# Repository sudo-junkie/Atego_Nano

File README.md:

# Atego Nano

KiCad 7 design files (schematic, PCB, gerber, BOM) for an Arduino Nano clone, with the following additional features:
-	Single cell lithium battery charger
-	VIN upto 15V
-	USB C
-	RGB LEDs

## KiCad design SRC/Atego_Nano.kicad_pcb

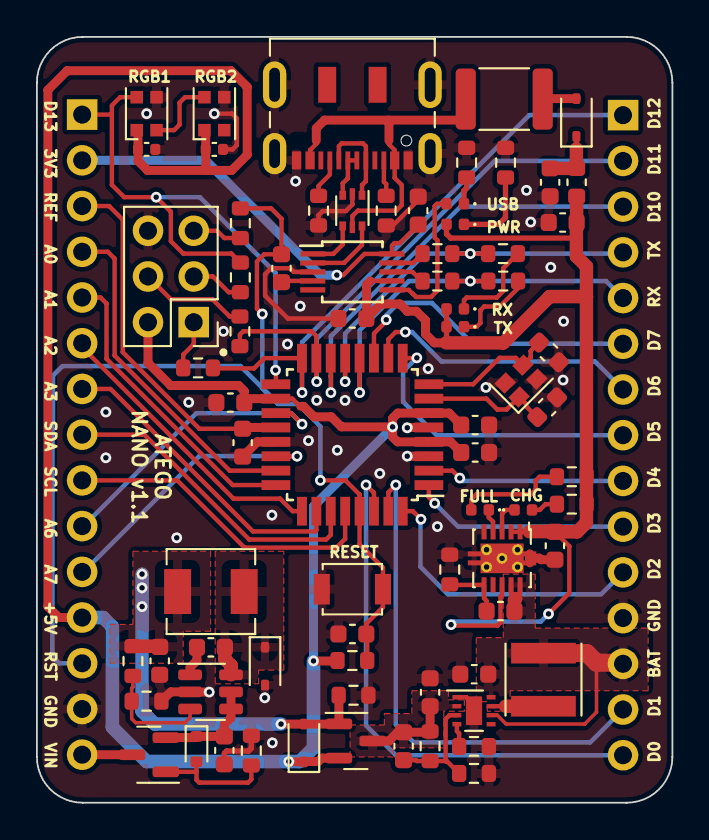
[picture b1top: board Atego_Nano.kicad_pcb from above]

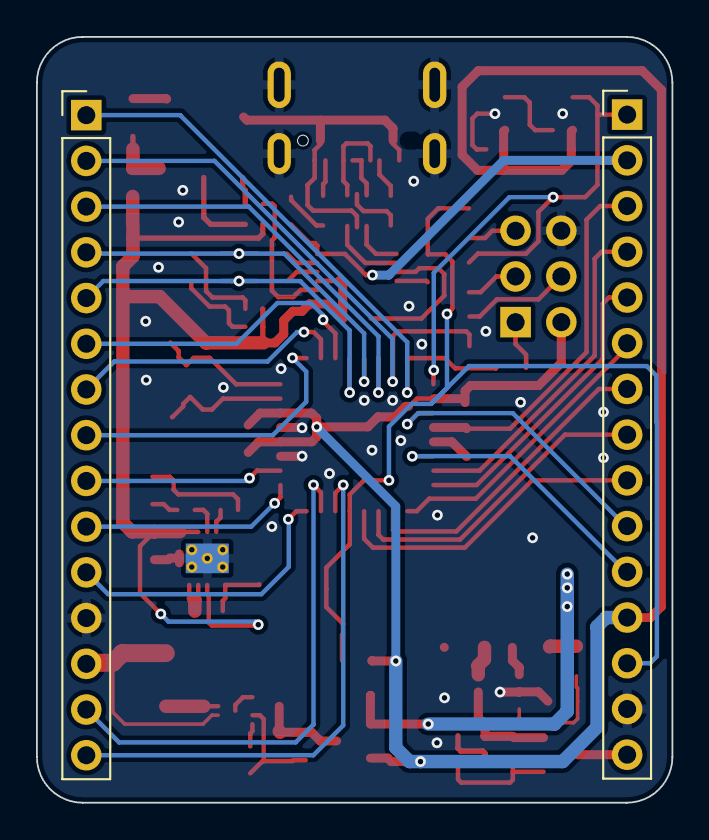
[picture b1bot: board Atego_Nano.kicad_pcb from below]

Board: 2 copper layers, 35.3 x 42.5 mm, 75 parts (2 on the bottom side), 69 nets.

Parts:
C101, C102, C602, C605, C606: 1u 10% 10V; C_0603_1608Metric
C301: 100p 1% 50V; C_0603_1608Metric
C302, C402: 10u 20% 25V; C_0603_1608Metric
C303, C403: 22u 20% 10V; C_0603_1608Metric
C401: 10n 10% 10V; C_0603_1608Metric
C501, C601, C603, C604, C701, C702: 100n 10% 10V; C_0603_1608Metric
C502: 470n 10% 16V; C_0603_1608Metric
C607, C608: 22p 1% 50V; C_0603_1608Metric
C609, C610: 100n 10V 5%; C_0402_1005Metric
D101, D202, D401: ES3A-ES3J; D_SOD-323
D201: LED_PWR; LED_0402_1005Metric
D203: 11V; D_SOD-523
D501: LED_R; LED_0402_1005Metric
D502: LED_G; LED_0402_1005Metric
D601, D602: WS2812B; LED_WS2812B-2020_PLCC4_2.0x2.0mm
D701: LED_USB_ACT; LED_0402_1005Metric
D702: LED_TX; LED_0402_1005Metric
D703: LED_RX; LED_0402_1005Metric
F101: 500mA; R_1812_4532Metric
FB101: 220R@100MHz 1.5A; L_0603_1608Metric
J101: USB_C_Receptacle_USB2.0; USB_C_Receptacle_JAE_DX07S016JA1R1500
J601: Conn_L; PinHeader_1x15_P2.54mm_Vertical
J602: Conn_R; PinHeader_1x15_P2.54mm_Vertical
J603: Conn_ICSP; PinHeader_2x03_P2.54mm_Vertical
L301: 1u; L_Vishay_IFSC-1515AH_4x4x1.8mm
L401: 4u7; L_Sunlord_MWSA0402S
Q201, Q202: AO3401A; SOT-23
R101, R102: 5K1 5%; R_0603_1608Metric
R201, R501, R502, R503, R602, R603, R604, R605, R701, R704, R705: 1K 0.1%; R_0603_1608Metric
R202, R203, R303, R601: 10K 0.1%; R_0603_1608Metric
R301: 768K; R_0603_1608Metric
R302: 243K; R_0603_1608Metric
R401: 180K 0.1%; R_0603_1608Metric
R402: 33K; R_0603_1608Metric
R702, R703: 470R 5%; R_0603_1608Metric
SW601: SW_RST; SW_SPST_B3U-1000P
U101: USBLC6-2P6; SOT-666
U301: TPS61252DSG; WSON-8-1EP_2x2mm_P0.5mm_EP0.9x1.6mm
U401: AP3211K; SOT-23-6
U501: BQ24012; VSON-10-1EP_3x3mm_P0.5mm_EP1.65x2.4mm_ThermalVias
U601: ATmega328P-A; TQFP-32_7x7mm_P0.8mm
U701: CH340E; MSOP-10_3x3mm_P0.5mm
Y601: 16MHz; Crystal_SMD_2016-4Pin_2.0x1.6mm

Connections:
+3V3: C702.1, J601.2, U701.10 (V3)
+5V: C601.1, C602.1, C603.1, C609.1, C610.1, D202.1 (K), D601.1 (VDD), D602.1 (VDD), J601.12, J603.2, Q201.2 (S), R601.1, U601.4 (VCC), U601.6 (VCC), U601.18 (AVCC)
+BATT: C302.1, C501.1, J602.13, L301.1, U301.6 (EN), U301.8 (VIN), U501.9 (BAT), U501.10 (OUT)
/ATEGO_NANO_POWER/5V_BOOST: C301.1, C303.1, Q201.3 (D), R301.1, U301.2 (VOUT)
/ATEGO_NANO_POWER/5V_BUCK: C403.1, D202.2 (A), L401.2, Q201.1 (G), R202.1, R401.1
/ATEGO_NANO_POWER/REGULATOR_SWITCHING_AP3221/FB: R401.2, R402.1, U401.3 (FB)
/ATEGO_NANO_POWER/REGULATOR_SWITCHING_AP3221/SW_5V: C401.2, D401.1 (K), L401.1, U401.6 (SW)
/ATEGO_NANO_POWER/REGULATOR_SWITCHING_TPS61252/SW: L301.2, U301.7 (SW)
/ATEGO_NANO_POWER/VIN: C402.1, D203.1 (K), Q202.2 (S), U401.4 (EN), U401.5 (IN)
/INTERFACE_USB_CH340E/CH340_D+: U101.4 (I/O2), U701.1 (UD+)
/INTERFACE_USB_CH340E/CH340_D-: U101.6 (I/O1), U701.2 (UD-)
/INTERFACE_USB_CH340E/CH340_RTS: C605.1, U701.4 (~RTS)
/INTERFACE_USB_CH340E/RXD: R704.2, U701.9 (RXD)
/INTERFACE_USB_CH340E/TXD: R705.2, U701.8 (TXD)
/MCU_ATMEGA328P-AU/A0: J601.4, U601.23 (PC0)
/MCU_ATMEGA328P-AU/A1: J601.5, U601.24 (PC1)
/MCU_ATMEGA328P-AU/A2: J601.6, U601.25 (PC2)
/MCU_ATMEGA328P-AU/A3: J601.7, U601.26 (PC3)
/MCU_ATMEGA328P-AU/A6: J601.10, U601.19 (ADC6)
/MCU_ATMEGA328P-AU/A7: J601.11, U601.22 (ADC7)
/MCU_ATMEGA328P-AU/AREF: C604.1, J601.3, U601.20 (AREF)
/MCU_ATMEGA328P-AU/ATMEGA_RX: J602.5, R703.2, R705.1, U601.12 (PB0)
/MCU_ATMEGA328P-AU/ATMEGA_TX: J602.4, R702.2, R704.1, U601.13 (PB1)
/MCU_ATMEGA328P-AU/D0: J602.15, U601.30 (PD0)
/MCU_ATMEGA328P-AU/D1: J602.14, U601.31 (PD1)
/MCU_ATMEGA328P-AU/D2: J602.11, U601.32 (PD2)
/MCU_ATMEGA328P-AU/D3: J602.10, U601.1 (PD3)
/MCU_ATMEGA328P-AU/D4: J602.9, U601.2 (PD4)
/MCU_ATMEGA328P-AU/D5: J602.8, U601.9 (PD5)
/MCU_ATMEGA328P-AU/D6: J602.7, U601.10 (PD6)
/MCU_ATMEGA328P-AU/D7: J602.6, U601.11 (PD7)
/MCU_ATMEGA328P-AU/D10: J602.3, U601.14 (PB2)
/MCU_ATMEGA328P-AU/D11: J602.2, R602.1, U601.15 (PB3)
/MCU_ATMEGA328P-AU/D12: J602.1, R605.2, U601.16 (PB4)
/MCU_ATMEGA328P-AU/D13: D601.4 (DIN), J601.1, R603.2, U601.17 (PB5)
/MCU_ATMEGA328P-AU/MISO: J603.1, R605.1
/MCU_ATMEGA328P-AU/MOSI: J603.4, R602.2
/MCU_ATMEGA328P-AU/NRST: C605.2, C606.1, J601.13, R601.2, R604.1, SW601.2, U601.29 (~RESET/PC6)
/MCU_ATMEGA328P-AU/RESET: J603.5, R604.2
/MCU_ATMEGA328P-AU/SCK: J603.3, R603.1
/MCU_ATMEGA328P-AU/SCL: J601.9, U601.28 (PC5)
/MCU_ATMEGA328P-AU/SDA: J601.8, U601.27 (PC4)
/MCU_ATMEGA328P-AU/X1: C607.1, U601.7 (XTAL1/PB6), Y601.1
/MCU_ATMEGA328P-AU/X2: C608.1, U601.8 (XTAL2/PB7), Y601.3
/VUSB: C102.1, C502.1, C701.1, D201.2 (A), D702.2 (A), D703.2 (A), FB101.2, R501.1, R502.1, U501.1 (IN), U501.2 (VCC), U501.8 (~CE), U701.7 (VCC)
GND: C101.2, C102.2, C302.2, C303.2, C402.2, C403.2, C502.2, C601.2, C602.2, C603.2, C604.2, C606.2, C607.2, C608.2, C609.2, C610.2, C701.2, C702.2, D401.2 (A), D601.3 (VSS), D602.3 (VSS), J101.A1 (GND), J101.A12 (GND), J101.B1 (GND), J101.B12 (GND), J101.S1 (SHIELD), J601.14, J602.12, J603.6, R101.2, R102.2, R201.2, R202.2, R203.2, R302.2, R303.2, R402.2, R503.2, R701.2, SW601.1, U101.2 (GND), U301.1 (GND), U301.9 (GND), U401.2 (GND), U501.5 (VSS), U501.11 (VSS), U601.3 (GND), U601.5 (GND), U601.21 (GND), U701.3 (GND), Y601.2, Y601.4
unnamed: D101.2 (A), F101.2
unnamed: C101.1, D101.1 (K), FB101.1
unnamed: D201.1 (K), R201.1
unnamed: D203.2 (A), Q202.1 (G), R203.1
unnamed: D501.2 (A), R502.2
unnamed: D501.1 (K), U501.3 (STAT1)
unnamed: D502.2 (A), R501.2
unnamed: D502.1 (K), U501.4 (STAT2)
unnamed: D601.2 (DOUT), D602.4 (DIN)
unnamed: D701.2 (A), U701.6 (TNOW)
unnamed: D701.1 (K), R701.1
unnamed: D702.1 (K), R702.1
unnamed: D703.1 (K), R703.1
unnamed: J101.A5 (CC1), R101.1
unnamed: J101.B5 (CC2), R102.1
unnamed: J101.A6 (D+), J101.B6 (D+), U101.3 (I/O2)
unnamed: J101.A7 (D-), J101.B7 (D-), U101.1 (I/O1)
unnamed: C301.2, R301.2, R302.1, U301.3 (FB)
unnamed: R303.1, U301.4 (ILIM)
unnamed: C401.1, U401.1 (BS)
unnamed: C501.2, R503.1, U501.6 (ISET)
VBUS: F101.1, J101.A4 (VBUS), J101.A9 (VBUS), J101.B4 (VBUS), J101.B9 (VBUS), U101.5 (VBUS)
VIN_12V: J601.15, Q202.3 (D)

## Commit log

2023-07-03 Corrected image in schematic
